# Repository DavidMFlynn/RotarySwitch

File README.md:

# RotarySwitch
 Electronic Rotary Switch

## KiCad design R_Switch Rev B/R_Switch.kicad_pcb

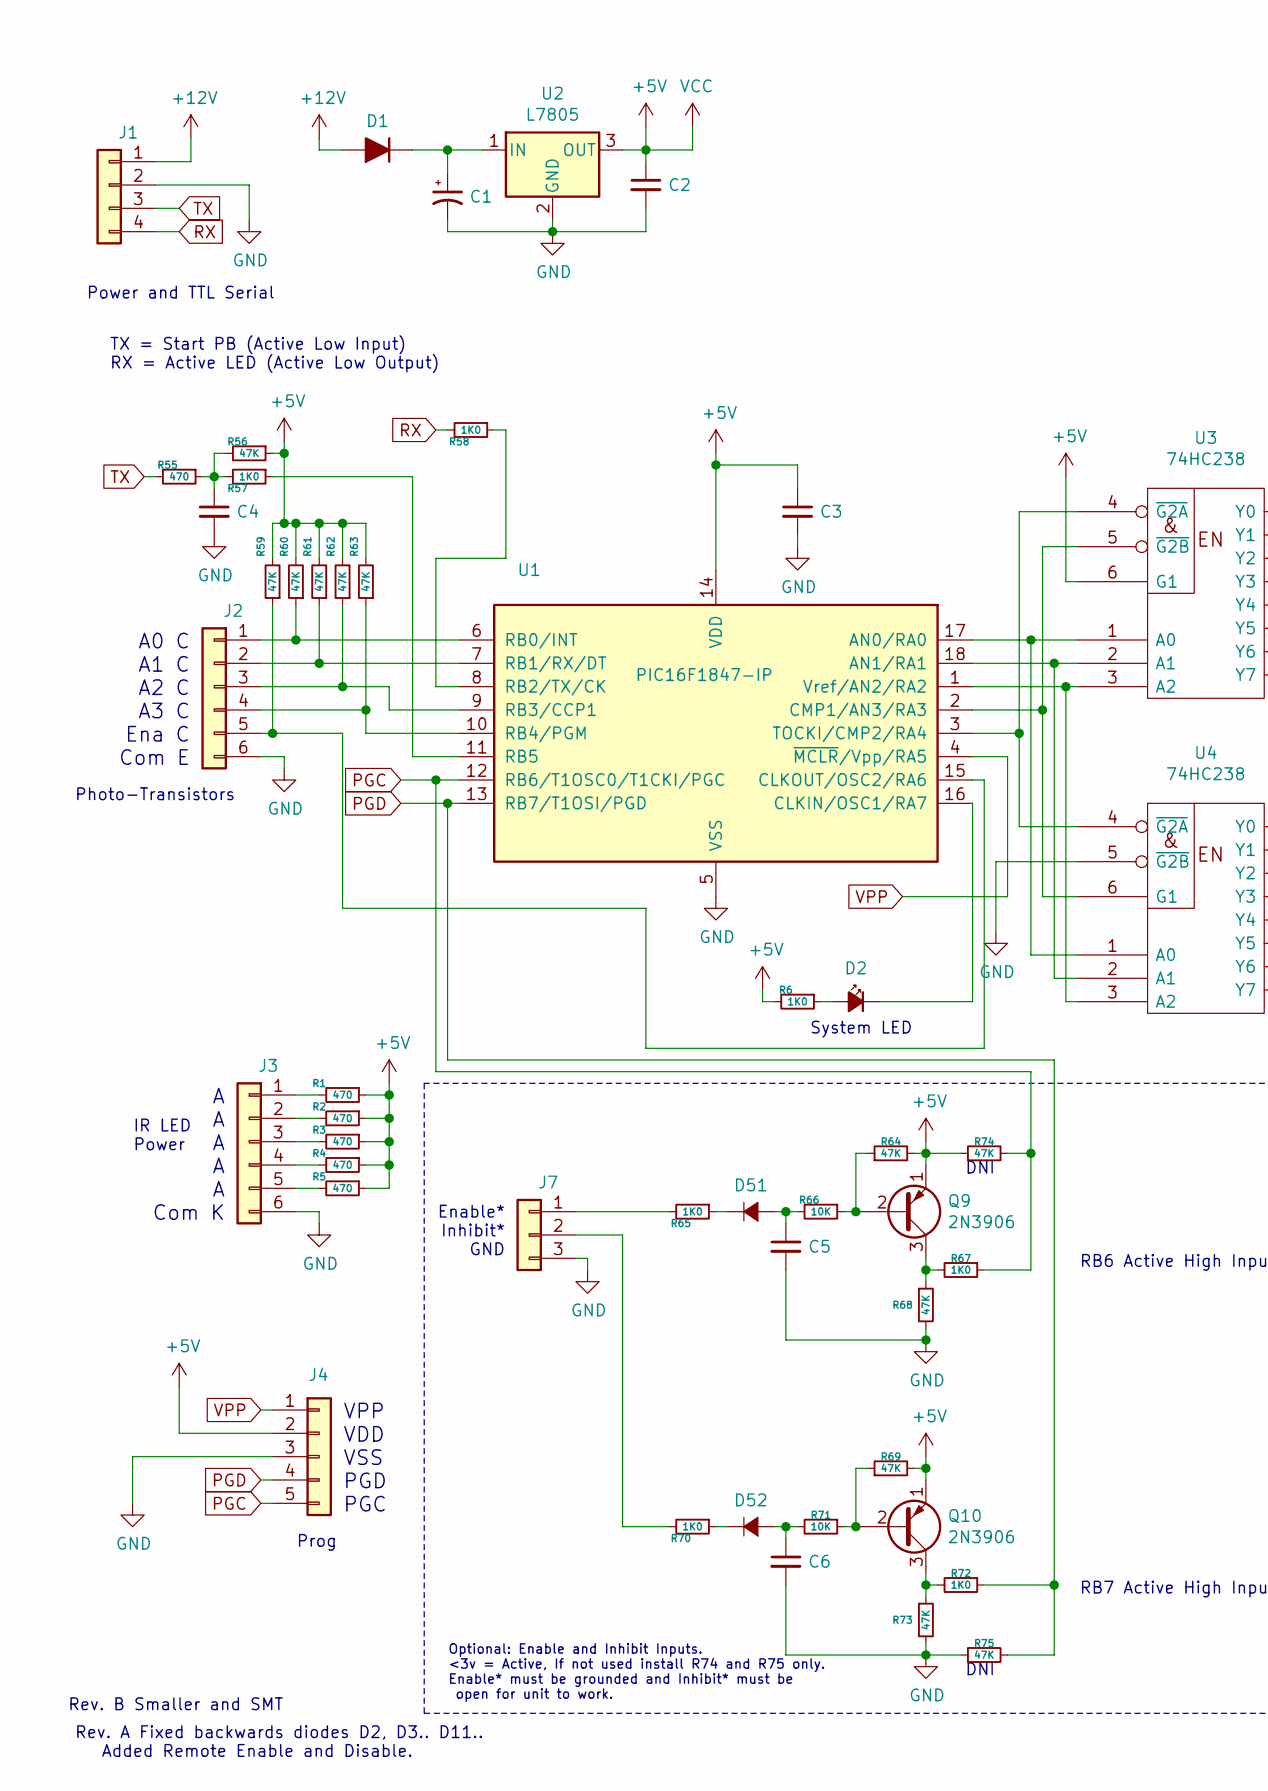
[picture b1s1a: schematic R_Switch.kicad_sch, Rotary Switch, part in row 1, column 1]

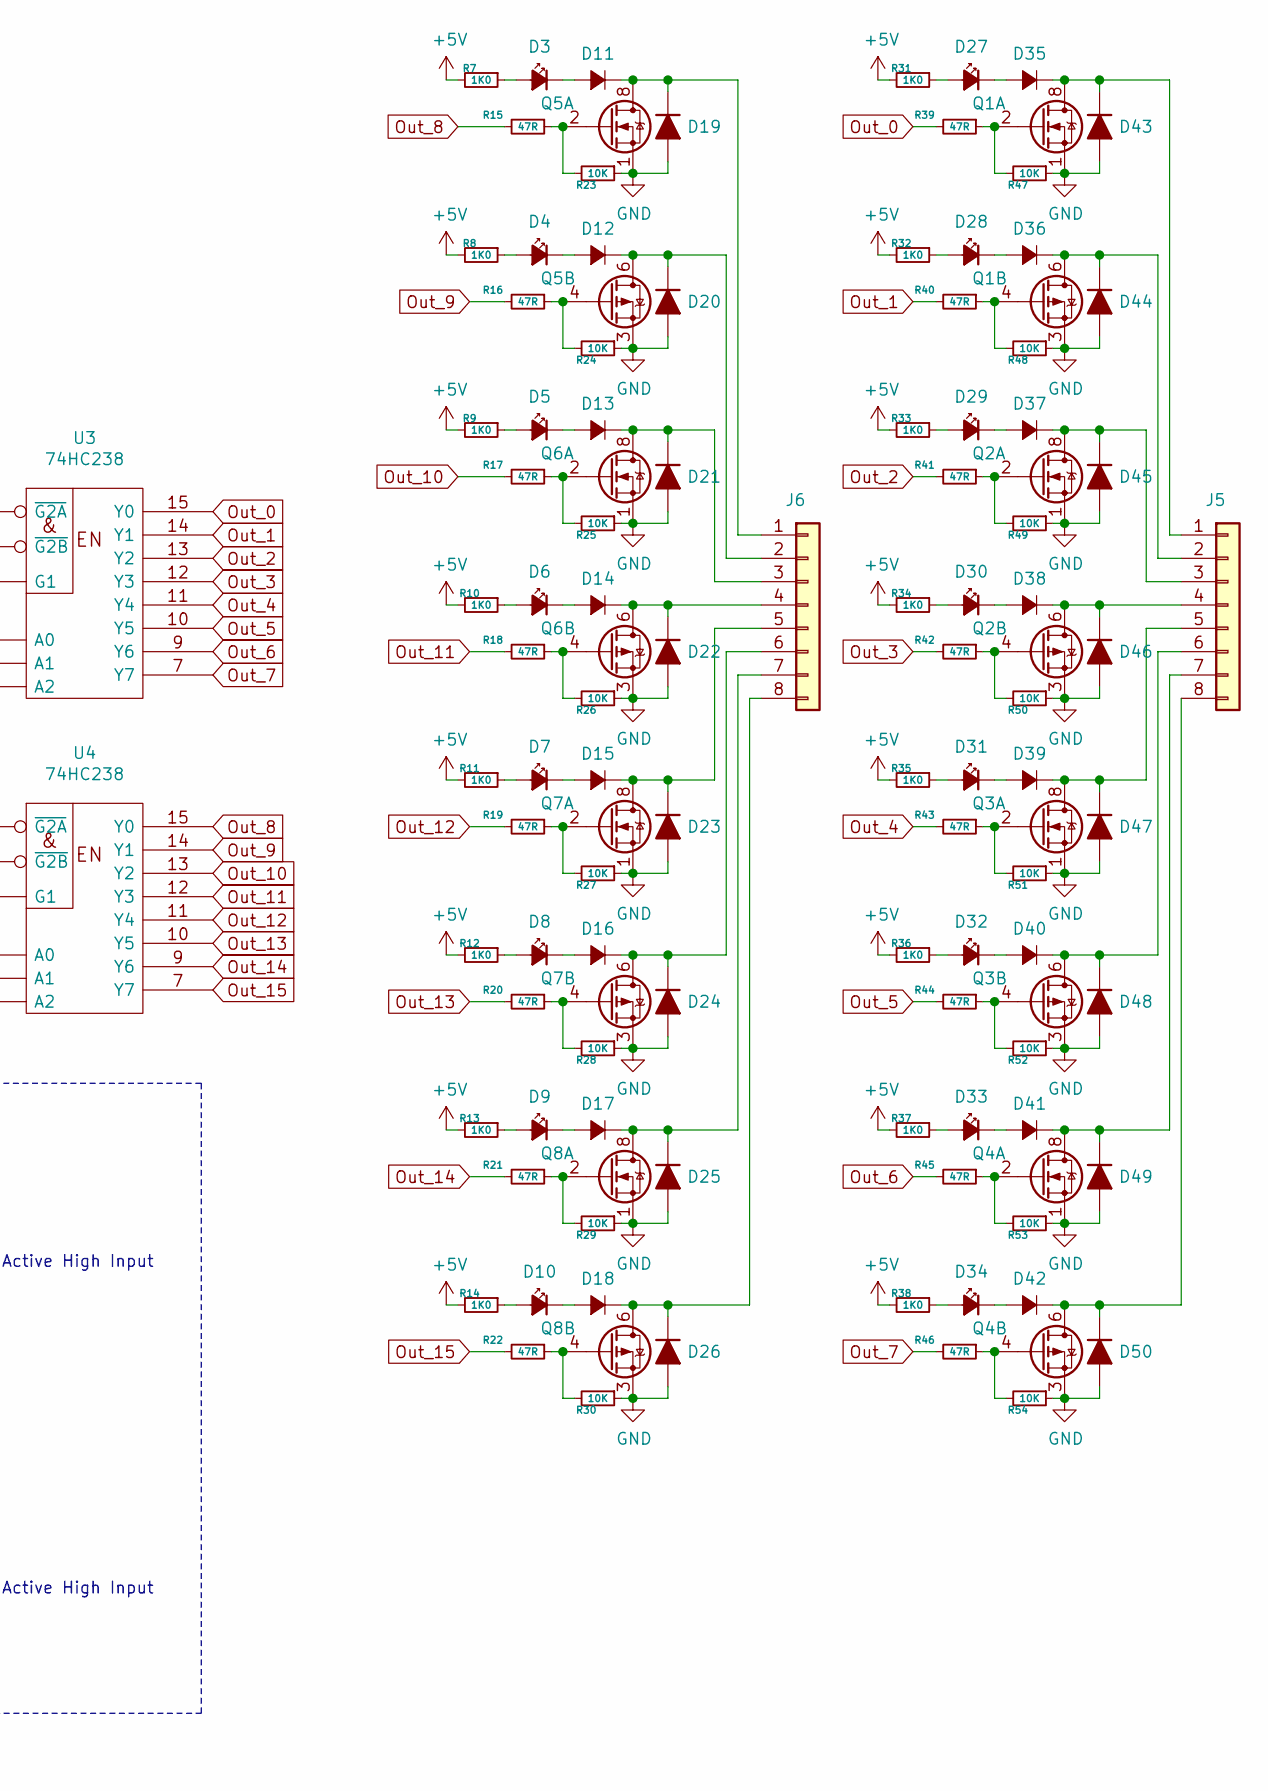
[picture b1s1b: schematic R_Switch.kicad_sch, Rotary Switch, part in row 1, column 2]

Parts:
C1: 4.7; CP_Radial_D5.0mm_P2.50mm
C2, C3, C4, C5, C6: 0.1; C_0805_2012Metric_Pad1.18x1.45mm_HandSolder
D1, D19, D20, D21, D22, D23, D24, D25, D26, D43, D44, D45, D46, D47, D48, D49, D50: D; D_SMA_Handsoldering
D2, D3, D4, D5, D6, D7, D8, D9, D10, D27, D28, D29, D30, D31, D32, D33, D34: LED_Small; LED_1206_3216Metric_Pad1.42x1.75mm_HandSolder
D11, D12, D13, D14, D15, D16, D17, D18, D35, D36, D37, D38, D39, D40, D41, D42, D51, D52: D_Small_ALT; D_SOD-123
J1: Conn_01x04; PhoenixContact_MSTBVA_2,5_4-G-5,08_1x04_P5.08mm_Vertical
J2, J3: Conn_01x06; PinHeader_1x06_P2.54mm_Vertical
J4: Conn_01x05; PinHeader_1x05_P2.54mm_Vertical
J5, J6: Conn_01x08; PhoenixContact_MSTBVA_2,5_8-G-5,08_1x08_P5.08mm_Vertical
J7: Conn_01x03; PhoenixContact_MSTBVA_2,5_3-G-5,08_1x03_P5.08mm_Vertical
Q1, Q2, Q3, Q4, Q5, Q6, Q7, Q8: IRF7343PBF; SOIC-8_3.9x4.9mm_P1.27mm
Q9, Q10: 2N3906; TO-92_Inline
R1, R2, R3, R4, R5, R55: 470; R_0805_2012Metric_Pad1.20x1.40mm_HandSolder
R6, R7, R8, R9, R10, R11, R12, R13, R14, R31, R32, R33, R34, R35, R36, R37, R38, R57, R58, R65, R67, R70, R72: 1K0; R_0805_2012Metric_Pad1.20x1.40mm_HandSolder
R15, R16, R17, R18, R19, R20, R21, R22, R39, R40, R41, R42, R43, R44, R45, R46: 47R; R_0805_2012Metric_Pad1.20x1.40mm_HandSolder
R23, R24, R25, R26, R27, R28, R29, R30, R47, R48, R49, R50, R51, R52, R53, R54, R66, R71: 10K; R_0805_2012Metric_Pad1.20x1.40mm_HandSolder
R56, R59, R60, R61, R62, R63, R64, R68, R69, R73, R74, R75: 47K; R_0805_2012Metric_Pad1.20x1.40mm_HandSolder
U1: PIC16F1847-IP; SOIC-18W_7.5x11.6mm_P1.27mm
U2: L7805; TO-252-2
U3, U4: 74HC238; SOP-16_3.9x9.9mm_P1.27mm

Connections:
+5V: C2.1, C3.1, J4.2, Q9.1 (E), Q10.1 (E), R1.1, R2.1, R3.1, R4.1, R5.1, R6.2, R7.2, R8.2, R9.2, R10.2, R11.2, R12.2, R13.2, R14.2, R31.2, R32.2, R33.2, R34.2, R35.2, R36.2, R37.2, R38.2, R56.1, R59.2, R60.2, R61.2, R62.2, R63.2, R64.2, R69.2, R74.1, U1.14 (VDD), U2.3 (OUT), U3.6 (G1), U3.16 (VCC), U4.16 (VCC)
+12V: D1.2 (A), J1.1
GND: C1.2, C2.2, C3.2, C4.2, C5.2, C6.2, D19.2 (A), D20.2 (A), D21.2 (A), D22.2 (A), D23.2 (A), D24.2 (A), D25.2 (A), D26.2 (A), D43.2 (A), D44.2 (A), D45.2 (A), D46.2 (A), D47.2 (A), D48.2 (A), D49.2 (A), D50.2 (A), J1.2, J2.6, J3.6, J4.3, J7.3, Q1.1 (S), Q1.3 (1), Q2.1 (S), Q2.3 (1), Q3.1 (S), Q3.3 (1), Q4.1 (S), Q4.3 (1), Q5.1 (S), Q5.3 (1), Q6.1 (S), Q6.3 (1), Q7.1 (S), Q7.3 (1), Q8.1 (S), Q8.3 (1), R23.1, R24.1, R25.1, R26.1, R27.1, R28.1, R29.1, R30.1, R47.1, R48.1, R49.1, R50.1, R51.1, R52.1, R53.1, R54.1, R68.2, R73.2, R75.1, U1.5 (VSS), U2.2 (GND), U3.8 (GND), U4.5 (~G2B), U4.8 (GND)
unnamed: C1.1, D1.1 (K), U2.1 (IN)
unnamed: C4.1, R55.1, R56.2, R57.2
unnamed: C5.1, D51.2 (A), R66.2
unnamed: C6.1, D52.2 (A), R71.2
unnamed: D2.1 (K), U1.16 (CLKIN/OSC1/RA7)
unnamed: D2.2 (A), R6.1
unnamed: D3.2 (A), R7.1
unnamed: D4.2 (A), R8.1
unnamed: D5.2 (A), R9.1
unnamed: D6.2 (A), R10.1
unnamed: D7.2 (A), R11.1
unnamed: D8.2 (A), R12.1
unnamed: D9.2 (A), R13.1
unnamed: D10.1 (K), D18.2 (A)
unnamed: D10.2 (A), R14.1
unnamed: D11.1 (K), D19.1 (K), J6.1, Q5.7 (D), Q5.8 (D)
unnamed: D3.1 (K), D11.2 (A)
unnamed: D12.1 (K), D20.1 (K), J6.2, Q5.5 (D), Q5.6 (D)
unnamed: D4.1 (K), D12.2 (A)
unnamed: D13.1 (K), D21.1 (K), J6.3, Q6.7 (D), Q6.8 (D)
unnamed: D5.1 (K), D13.2 (A)
unnamed: D14.1 (K), D22.1 (K), J6.4, Q6.5 (D), Q6.6 (D)
unnamed: D6.1 (K), D14.2 (A)
unnamed: D15.1 (K), D23.1 (K), J6.5, Q7.7 (D), Q7.8 (D)
unnamed: D7.1 (K), D15.2 (A)
unnamed: D16.1 (K), D24.1 (K), J6.6, Q7.5 (D), Q7.6 (D)
unnamed: D8.1 (K), D16.2 (A)
unnamed: D17.1 (K), D25.1 (K), J6.7, Q8.7 (D), Q8.8 (D)
unnamed: D9.1 (K), D17.2 (A)
unnamed: D18.1 (K), D26.1 (K), J6.8, Q8.5 (D), Q8.6 (D)
unnamed: D27.1 (K), D35.2 (A)
unnamed: D27.2 (A), R31.1
unnamed: D28.1 (K), D36.2 (A)
unnamed: D28.2 (A), R32.1
unnamed: D29.1 (K), D37.2 (A)
unnamed: D29.2 (A), R33.1
unnamed: D30.1 (K), D38.2 (A)
unnamed: D30.2 (A), R34.1
unnamed: D31.1 (K), D39.2 (A)
unnamed: D31.2 (A), R35.1
unnamed: D32.1 (K), D40.2 (A)
unnamed: D32.2 (A), R36.1
unnamed: D33.1 (K), D41.2 (A)
unnamed: D33.2 (A), R37.1
unnamed: D34.1 (K), D42.2 (A)
unnamed: D34.2 (A), R38.1
unnamed: D35.1 (K), D43.1 (K), J5.1, Q1.7 (D), Q1.8 (D)
unnamed: D36.1 (K), D44.1 (K), J5.2, Q1.5 (D), Q1.6 (D)
unnamed: D37.1 (K), D45.1 (K), J5.3, Q2.7 (D), Q2.8 (D)
unnamed: D38.1 (K), D46.1 (K), J5.4, Q2.5 (D), Q2.6 (D)
unnamed: D39.1 (K), D47.1 (K), J5.5, Q3.7 (D), Q3.8 (D)
unnamed: D40.1 (K), D48.1 (K), J5.6, Q3.5 (D), Q3.6 (D)
unnamed: D41.1 (K), D49.1 (K), J5.7, Q4.7 (D), Q4.8 (D)
unnamed: D42.1 (K), D50.1 (K), J5.8, Q4.5 (D), Q4.6 (D)
unnamed: D51.1 (K), R65.1
unnamed: D52.1 (K), R70.1
unnamed: J2.1, R60.1, U1.6 (RB0/INT)
unnamed: J2.2, R61.1, U1.7 (RB1/RX/DT)
unnamed: J2.3, R62.1, U1.9 (RB3/CCP1)
unnamed: J2.4, R63.1, U1.10 (RB4/PGM)
unnamed: J2.5, R59.1, U1.15 (CLKOUT/OSC2/RA6)
unnamed: J3.1, R1.2
unnamed: J3.2, R2.2
unnamed: J3.3, R3.2
unnamed: J3.4, R4.2
unnamed: J3.5, R5.2
unnamed: J7.1, R65.2
unnamed: J7.2, R70.2
unnamed: Q1.2 (G), R39.1, R47.2
unnamed: Q1.4 (G), R40.1, R48.2
unnamed: Q2.2 (G), R41.1, R49.2
unnamed: Q2.4 (G), R42.1, R50.2
unnamed: Q3.2 (G), R43.1, R51.2
unnamed: Q3.4 (G), R44.1, R52.2
unnamed: Q4.2 (G), R45.1, R53.2
unnamed: Q4.4 (G), R46.1, R54.2
unnamed: Q5.2 (G), R15.1, R23.2
unnamed: Q5.4 (G), R16.1, R24.2
unnamed: Q6.2 (G), R17.1, R25.2
unnamed: Q6.4 (G), R18.1, R26.2
unnamed: Q7.2 (G), R19.1, R27.2
unnamed: Q7.4 (G), R20.1, R28.2
unnamed: Q8.2 (G), R21.1, R29.2
unnamed: Q8.4 (G), R22.1, R30.2
unnamed: Q9.2 (B), R64.1, R66.1
unnamed: Q9.3 (C), R67.2, R68.1
unnamed: Q10.2 (B), R69.1, R71.1
unnamed: Q10.3 (C), R72.2, R73.1
unnamed: R57.1, U1.11 (RB5)
unnamed: R58.1, U1.8 (RB2/TX/CK)
unnamed: U1.1 (Vref/AN2/RA2), U3.3 (A2), U4.3 (A2)
unnamed: U1.2 (CMP1/AN3/RA3), U3.5 (~G2B), U4.6 (G1)
unnamed: U1.3 (TOCKI/CMP2/RA4), U3.4 (~G2A), U4.4 (~G2A)
unnamed: U1.17 (AN0/RA0), U3.1 (A0), U4.1 (A0)
unnamed: U1.18 (AN1/RA1), U3.2 (A1), U4.2 (A1)
Out_0: R39.2, U3.15 (Y0)
Out_1: R40.2, U3.14 (Y1)
Out_2: R41.2, U3.13 (Y2)
Out_3: R42.2, U3.12 (Y3)
Out_4: R43.2, U3.11 (Y4)
Out_5: R44.2, U3.10 (Y5)
Out_6: R45.2, U3.9 (Y6)
Out_7: R46.2, U3.7 (Y7)
Out_8: R15.2, U4.15 (Y0)
Out_9: R16.2, U4.14 (Y1)
Out_10: R17.2, U4.13 (Y2)
Out_11: R18.2, U4.12 (Y3)
Out_12: R19.2, U4.11 (Y4)
Out_13: R20.2, U4.10 (Y5)
Out_14: R21.2, U4.9 (Y6)
Out_15: R22.2, U4.7 (Y7)
PGC: J4.5, R67.1, R74.2, U1.12 (RB6/T1OSC0/T1CKI/PGC)
PGD: J4.4, R72.1, R75.2, U1.13 (RB7/T1OSI/PGD)
RX: J1.4, R58.2
TX: J1.3, R55.2
VPP: J4.1, U1.4 (~MCLR~/Vpp/RA5)

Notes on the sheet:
Photo-Transistors
Rev. A Fixed backwards diodes D2, D3.. D11.. Added Remote Enable and Disable.
Power and TTL Serial
TX = Start PB (Active Low Input) RX = Active LED (Active Low Output)
IR LED Power
A0 C A1 C A2 C A3 C Ena C Com E
A A A A A Com K
Rev. B Smaller and SMT
Prog
VPP VDD VSS PGD PGC
Optional: Enable and Inhibit Inputs. <3v = Active, If not used install R74 and R75 only. Enable* must be grounded and Inhibit* must be open for unit to work.
Enable* Inhibit* GND
System LED
DNI
RB6 Active High Input
RB7 Active High Input

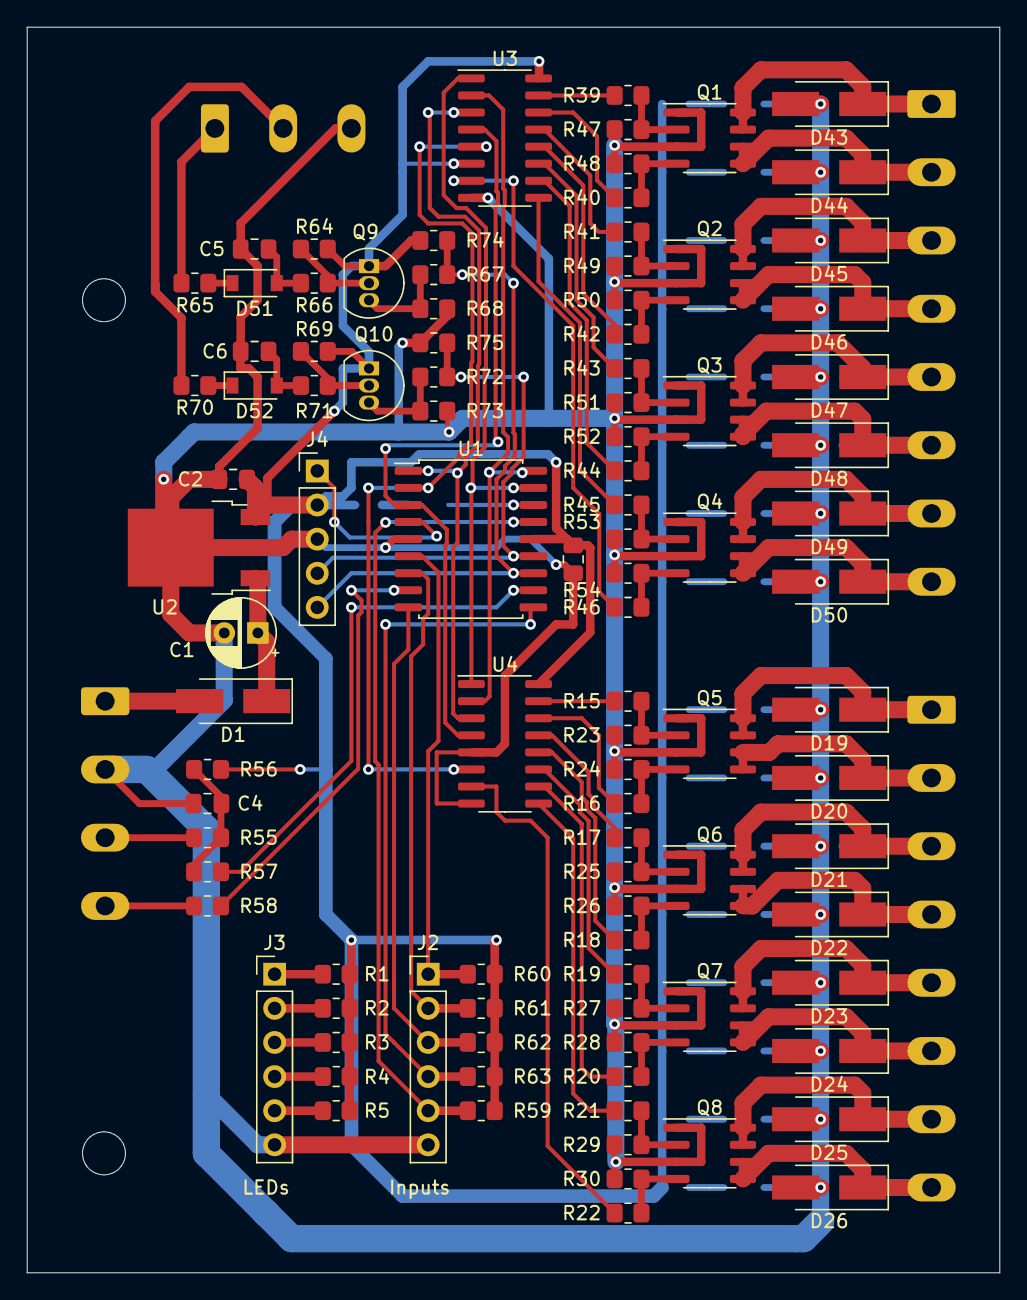
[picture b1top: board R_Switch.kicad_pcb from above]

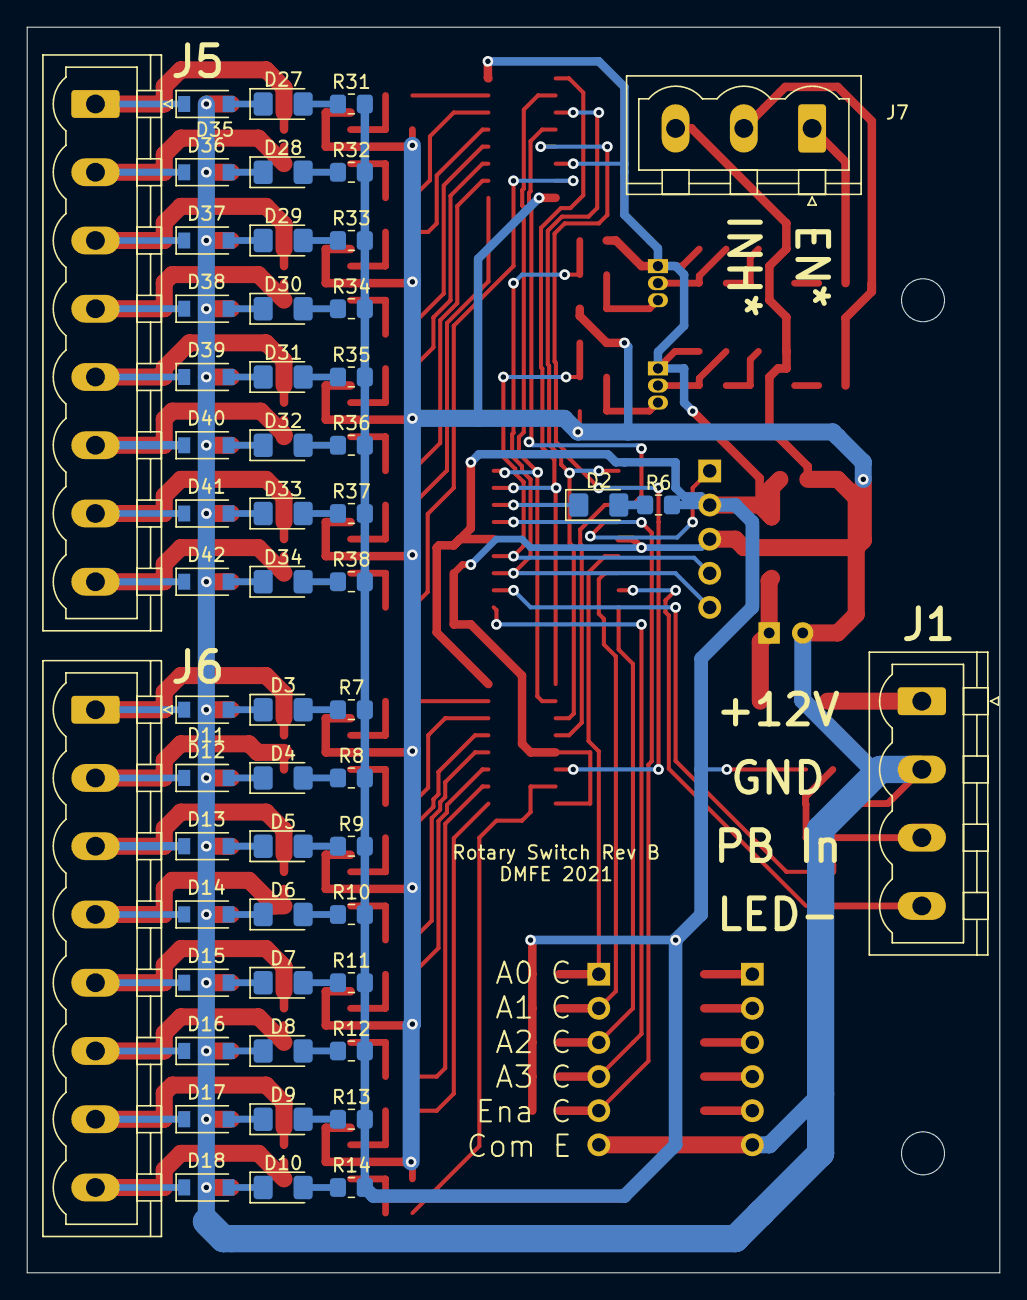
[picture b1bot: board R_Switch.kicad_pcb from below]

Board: 2 copper layers, 72.4 x 92.7 mm, 156 parts (54 on the bottom side), 119 nets.

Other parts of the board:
H1, H2: MountingHole_3.2mm_M3

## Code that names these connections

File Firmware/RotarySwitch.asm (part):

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;      If input does not match setting the fast blink Active LED.
;====================================================================================================
;
;   Pin 1 (RA2/AN2) Output A2 (Digital Output)
;   Pin 2 (RA3/AN3) Output A3 (Digital Output)
;   Pin 3 (RA4/AN4) Output Enable (Active Low Output)
;   Pin 4 (RA5/MCLR*) VPP/MCLR*
;   Pin 5 (GND) Ground
;   Pin 6 (RB0) Input A0 (Active Low Input)
;   Pin 7 (RB1/AN11/SDA1) Input A1 (Active Low Input)
;   Pin 8 (RB2/AN10/TX) RX (Optional, future feature) or Active LED (Active High Output)
;   Pin 9 (RB3/CCP1) Input A2 (Active Low Input)
;
;   Pin 10 (RB4/AN8/SLC1) Input A3 (Active Low Input)
;   Pin 11 (RB5/AN7) Start Button (Active Low Input)
;   Pin 12 (RB6/AN5/CCP2) ICSPCLK
;   Pin 13 (RB7/AN6) ICSPDAT
;   Pin 14 (Vcc) +5 volts
;   Pin 15 (RA6) Input Enable (Active Low Input)
;   Pin 16 (RA7/CCP2) System LED (Active Low Output)(System LED)
;   Pin 17 (RA0/AN0) Output A0 (Digital Output)
;   Pin 18 (RA1) Output A1 (Digital Output)
;
;====================================================================================================
;
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; INTOSC oscillator: I/O function on CLKIN pin
; WDT disabled
; PWRT disabled
; MCLR/VPP pin function is digital input
; Program memory code protection is disabled
; Data memory code protection is disabled
; Brown-out Reset enabled
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#Define	OUT_A2	LATA,2	;Output A2 (Digital Output)
#Define	OUT_A3	LATA,3	;Output A3 (Digital Output)
#Define	OUT_Enable	LATA,4	;Output Enable (Active Low Output)
#Define	RA5_In	PORTA,5	;VPP/MCLR*
#Define	In_Enable	PORTA,6	;Input Enable (Active Low Input)
#Define	RA7_In	PORTA,7	;Sys LED D2 System LED
SysLED_Bit	EQU	7	;Sys LED (Active Low Output)
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
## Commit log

2019-07-25 Enable and inhibit inputs
2019-08-07 14 stops
2019-08-11 CW16
2019-08-11 ignore gcode
2019-08-19 magnet detents
2019-12-07 Ordered Rev A
2021-01-06 Created parts list
2021-05-07 Rev B PCB (Smaller)
2021-05-11 n7 and n9
2021-05-18 more n's
